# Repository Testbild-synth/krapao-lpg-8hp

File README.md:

# Voxmachina Krapao Resonant Low Pass Gate - now in 8HP
This repository contains the files for a narrower version of the great 
[Krapao low pass gate](https://www.youtube.com/watch?v=gdqPUZgIWGM&t=87s) module from voxmachina.

I would say my version is more of a bootleg/edit more than actually changing much here.

## Status: confirmed working!

## Hardware and ordering
The repo has three gerbers, one is the panel, one is the control pcb, one is the "main pcb" which basically 
only contains the vactrols. Just order one of each at a pcb service of your choice (I use jlcpcb.com).

BOM is the same as original krapao, I have a csv file but it'S not very tidy. All pots are R09k type (I make the holes
bigger because the chinese knock offs have bigger legs) all jacks are thonkiconn.

Instead of ordering VTL5C3 vactrols (which are expensive) I would recommend making your own using
a simple LED, some shrink tubing and an LDR. There are a ton of tutorials out there just google DIY vactrol.

the big switch is a 3dpt, somethings like [this](https://www.musikding.de/Toggleswitch-3PDT-on-off-on). There are a wide variety,
idk which one is the best but ideally it should be the lowest you can get (because it does stand out a bit further than the thonkiconn jacks which makes the whole module
tilt at a slight angle). Not sure how voxmachina does this but on mine it's still fine and not that noticable in the final module.
the big 3dpt is ON-OFF-ON, the smaller spdt is ON-ON.

## Build
Since the build is a bit crammy on 8hp there are a few places where you have to think about what order you solder things in.
Most notably the LED in the front that is on the backside of a TL074. Nothing horrible, just take it slow.

Earlier versions had the problem of things on the control pcb and the vactrol pcb sticking out and being in the
way of each other. This should be resolved by now.

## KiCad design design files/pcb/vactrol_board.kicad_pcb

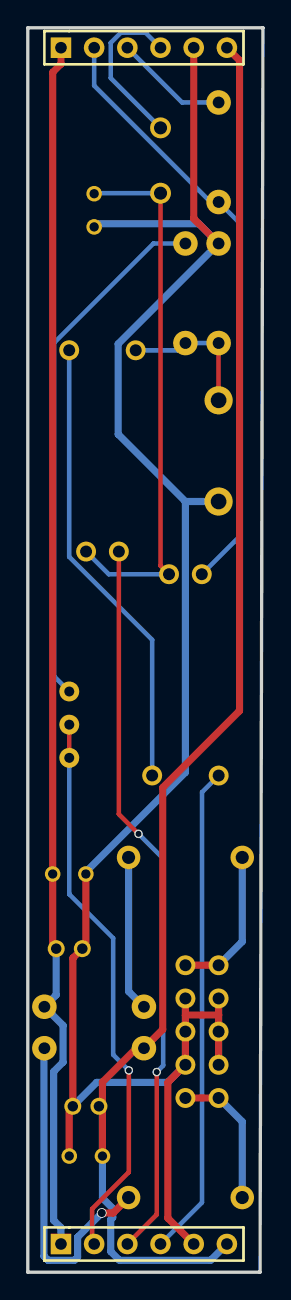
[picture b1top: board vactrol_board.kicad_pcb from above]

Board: 2 copper layers, 18.0 x 95.2 mm, 20 parts (0 on the bottom side), 17 nets.

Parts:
C1: 220pf; RAD-0.1
C3, C5: 47uF; CAP-TH_BD5.0-P2.00-D0.8-FD
C4, C6: 0.1uf; RAD-0.1
C8: 4.7nF; CAP-TH_L6.5-W2.5-P5.00-D1.0
D1: 1N4730A; DO-41
D2, D3: 1N5819; DO-41_BD2.4-L4.7-P8.70-D0.9-RD
H1: TOP; HDR-F-2.54_1X6
H2: BOT; HDR-F-2.54_1X6
P1: POWER; EURORACK SHROUDED POWER 10 PIN
R1: 33k; AXIAL-0.3EZ
R2: 100k; AXIAL-0.3EZ
R3: 10k; AXIAL-0.3EZ
R4, R5: 10; AXIAL-0.3EZ
TM1: 20k; TRIMPOT
U1, U2: VTL5C4

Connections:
+12V: C3.1, C4.2, H1.1, H2.1, R4.2
-12V: C5.2, C6.1, H1.6, H2.6, R5.2
AUDIOIN1: H2.3, U1.4
CVIN6: H2.2, TM1.2, TM1.3
CVIN7: H2.4, U2.1
D2_1: D2.1, R4.1
D3_2: D3.2, R5.1
GND: C1.2, C3.2, C4.1, C5.1, C6.2, D1.2, H1.5, H2.5, P1.2, P1.3, P1.4, R2.1
P1_1: D2.2, P1.1
P1_5: D3.1, P1.5
R1_2: R1.2, TM1.1
U1_2: D1.1, R1.1, R2.2, U1.2
U2_2: U1.1, U2.2
U2_4: C1.1, C8.1, U1.3, U2.4
VCA3: H1.3, R3.2
VCAOUT: H1.2, R3.1, U2.3
VCF1: C8.2, H1.4

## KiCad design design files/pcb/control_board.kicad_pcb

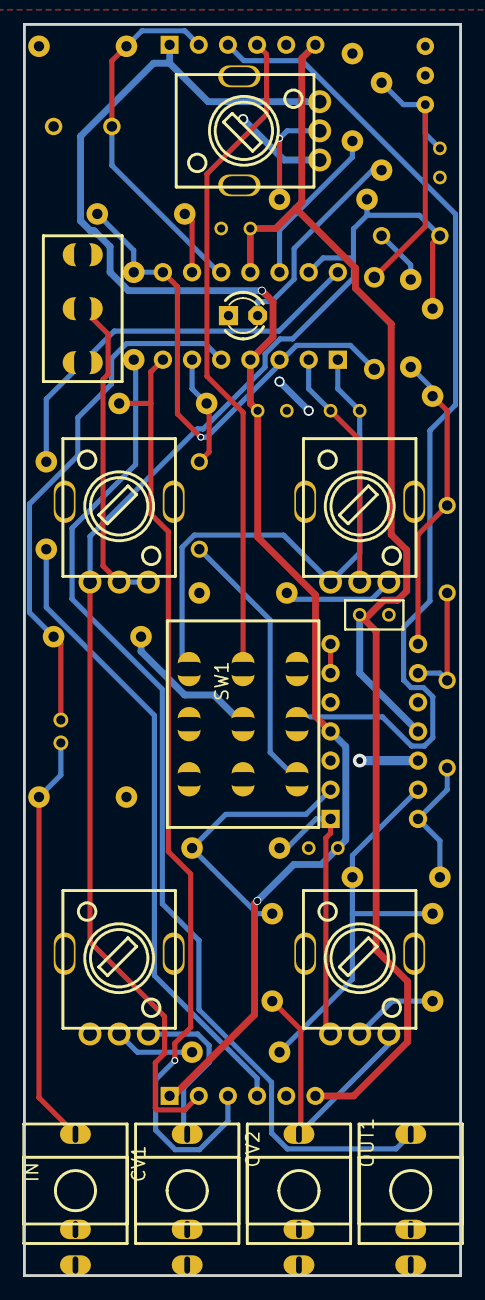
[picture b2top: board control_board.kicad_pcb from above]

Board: 2 copper layers, 38.0 x 109.0 mm, 48 parts (0 on the bottom side), 37 nets.

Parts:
C1: 1nf; CAP FILM KEMET 2.5*7.2
C2: 1uF; CAP-TH_BD5.0-P2.00-D0.8-FD
C3: 22pf; RAD-0.1
C4: 2nf; CAP FILM KEMET 2.5*7.2
C5, C6, C7, C8: 0.1uf; RAD-0.1
C9: 1uF; RAD-0.1
CV1: CV 1 IN; THONKICONN
CV1_ADJ, CV2_ADJ: 100k; R09-5KΩ
CV2: CV 2 IN; THONKICONN
D1: 1N4148; DO-35_BD2.0-L4.0-P8.00-D0.5-FD
DEEP_POT: 500k; R09-5KΩ
H1: HTOP; HDR-F-2.54_1X6
H2: HBOT; HDR-F-2.54_1X6
IN: AUDIO IN; THONKICONN
LED1: LED; LED_LED3MM
LED_ADJ: 10k; TRIMPOT
OFFSET_POT: 100k; R09-5KΩ
OUT1: AUDIO OUT; THONKICONN
R1: 1k; AXIAL-0.3EZ
R2: 4M7; AXIAL-0.3EZ
R3, R10, R19: 10k; AXIAL-0.3EZ
R4, R5: 15k; AXIAL-0.3EZ
R6, R7, R9, R11, R15, R16, R17, R21, R22, R24: 100k; AXIAL-0.3EZ
R8: 2k2; AXIAL-0.3EZ
R14: 150k; AXIAL-0.3EZ
R18: 470k; AXIAL-0.3EZ
R23: 470; AXIAL-0.3EZ
RES_POT: 100k; R09-5KΩ
SW1: MODE; (TAYDA) MINI TOGGLE SWITCH 3PDT ON-ON SKU A-1955
SW2: DAMP; TAYDA SPDT TOGGLE SWITCH A-3670_LARGERHOLES
U1: TL084; DIP-14
U2: TL074; DIP-14

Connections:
+12V: C5.2, C6.2, H1.1, H2.1, OFFSET_POT.3, U1.4, U2.4
-12V: C7.1, C8.1, H1.6, H2.6, U1.11, U2.11
AGND: C1.1, C5.1, C6.1, C7.2, C8.2, C9.1, CV1.1, CV1.2, CV1_ADJ.1, CV2.1, CV2.2, H1.5, H2.5, IN.1, IN.2, LED1.-, LED_ADJ.2, LED_ADJ.3, OFFSET_POT.1, OUT1.1, R2.2, R6.2, R7.2, R10.2, R19.1, SW1.2, SW1.5, U2.3, U2.5, U2.10, U2.12
AUDIOIN1: H2.3, R5.1, U1.7
C2_1: C2.1, IN.3, R6.1
C3_1: C3.1, RES_POT.2, U1.2
CV1_3: CV1.3, CV1_ADJ.3
CVIN6: C4.1, DEEP_POT.1, H2.2, R14.1, R24.1, U1.13
CVIN7: H2.4, R23.1
D1_2: C9.2, D1.2, LED_ADJ.1, R8.2
LED1_+: LED1.+, R8.1
OUT1_3: OUT1.3, R1.1
R1_2: D1.1, R1.2, R3.1, U1.3, U1.8
R3_2: R3.2, U1.9
R4_2: R4.2, R5.2, U1.6
R7_1: C2.2, R7.1, U1.5
R9_1: CV2_ADJ.1, R9.1, U2.1
R9_2: R9.2, R11.1, U2.2
R10_1: R10.1, RES_POT.3
R11_2: CV2.3, CV2_ADJ.3, R11.2
R14_2: OFFSET_POT.2, R14.2
R15_1: R15.1, R16.2, R21.1, U2.13
R15_2: CV2_ADJ.2, R15.2
R17_2: R17.2, R22.1, U2.9
R18_1: C4.2, R18.1
R18_2: R17.1, R18.2, R24.2, U2.8
R19_2: R19.2, U1.12
R21_2: CV1_ADJ.2, R21.2
R22_2: R16.1, R22.2, U2.14
R23_2: R23.2, SW2.3, U1.14
SW2_2: DEEP_POT.2, DEEP_POT.3, SW2.2
U2_6: U2.6, U2.7
VCA1: R4.1, SW1.3
VCA3: H1.3, SW1.6
VCAOUT: C1.2, H1.2, R2.1, U1.10
VCF1: H1.4, SW1.8
VCF2: C3.2, RES_POT.1, SW1.7, U1.1

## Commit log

2024-12-25 initial file upload
2024-12-26 clarified switch choice in BOM
